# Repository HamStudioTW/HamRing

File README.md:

```                                                                     
  ╭──╮                        ╭──────────────────╮                  
  |  |                        |  ╭────────────╮  |        ╭──────────╮          
  |  │            ╭──╮        |  |            |  |        |  ╭────╮  ╰───────╮  
  |  ╰────────────╯  |        |  ╰────────────╯  |        |  |    |  ╭────╮  |  
  |  ╭────────────╮  |        |  ╭────────────╮  |        |  |    |  |    |  |  
  |  │            │  |        |  │            │  |        |  |    |  |    |  |  
  |  │            │  |        |  │            │  |        |  |    |  |    |  | 
  ╰──╯            ╰──╯        ╰──╯            ╰──╯        ╰──╯    ╰──╯    ╰──╯  Studio
```
# HamRing

"Keychain_Main" is base on ATTiny84a useing Micronucleus Bootloader  
"ESP_Keychain"  is base on ESP-M1(ESP8285) useing Arduino Bootloader  
"AnyWare8051" is base on STC8G1K08  
"OneKey" is base on CH552G useing Arduino Bootloader

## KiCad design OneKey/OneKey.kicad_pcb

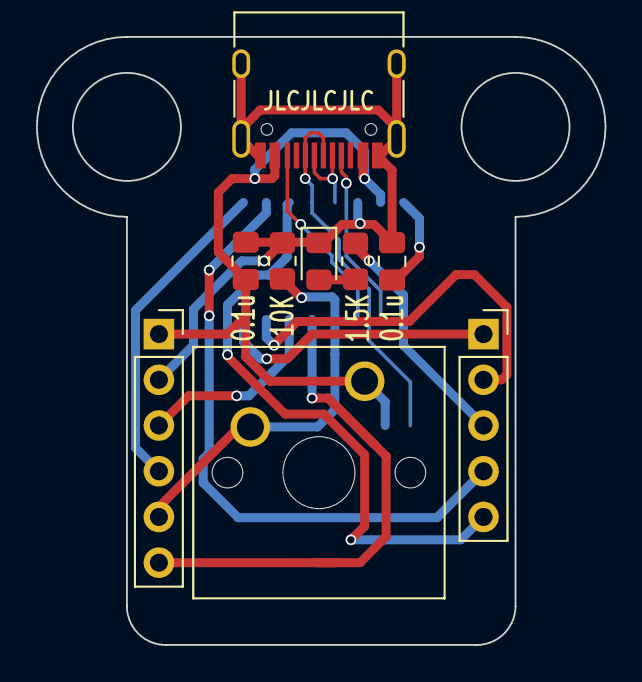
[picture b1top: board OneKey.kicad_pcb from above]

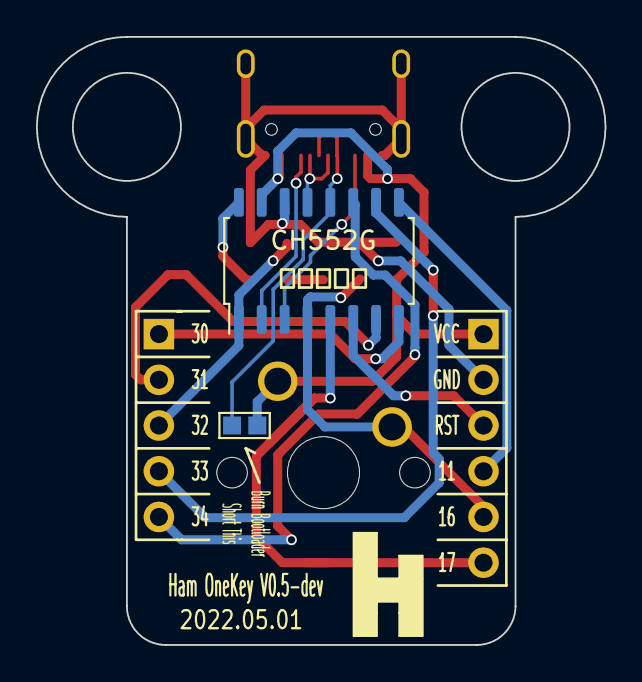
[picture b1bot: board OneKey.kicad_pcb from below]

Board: 2 copper layers, 31.6 x 33.8 mm, 12 parts (3 on the bottom side), 17 nets.

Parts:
0.1u, 0.1u#2: 0.1u; C_0805_2012Metric_Pad1.18x1.45mm_HandSolder
1.5K: 1.5K; R_0805_2012Metric_Pad1.20x1.40mm_HandSolder
10K: 10K; R_0805_2012Metric_Pad1.20x1.40mm_HandSolder
CH552G: CH552G; SOIC-16_4.55x10.3mm_P1.27mm
D1: LED; D_0805_2012Metric_Pad1.15x1.40mm_HandSolder
D+: TestPoint_Pad_1.0x1.0mm
J1: USB_C_Receptacle_USB2.0; USB_C_Receptacle_HRO_TYPE-C-31-M-12
J2: Conn_01x06_Female; PinSocket_1x06_P2.54mm_Vertical
J3: Conn_01x05_Female; PinSocket_1x05_P2.54mm_Vertical
SW1: SW_Push; SW_Cherry_MX_1.00u_PCB
VCC: TestPoint_Pad_1.0x1.0mm

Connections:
D+: CH552G.12 (P3.6/UDP), D+.1, J1.A6 (D+), J1.B6 (D+)
D-: CH552G.13 (P3.7/UDM), J1.A7 (D-), J1.B7 (D-)
GND: 0.1u.1, 0.1u#2.1, 10K.1, CH552G.14 (GND), D1.1 (K), J1.A1 (GND), J1.A12 (GND), J1.B1 (GND), J1.B12 (GND), J1.S1 (SHIELD), J2.2
unnamed: 0.1u.2, CH552G.16 (V33)
unnamed: 1.5K.1, D1.2 (A)
P1.1: CH552G.9 (P1.1), J2.4
P1.6: 10K.2, CH552G.4 (P1.6/MISO/RxD1_), J2.5, SW1.2
P1.7: CH552G.5 (P1.7/SCK/TxD1), J2.6
P3.0: CH552G.8 (P3.0/RxD), J3.1
P3.1: CH552G.7 (P3.1/TxD), J3.2
P3.2: 1.5K.2, CH552G.1 (P3.2/TxD1_), J3.3
P3.3: CH552G.10 (P3.3), J3.4
P3.4: CH552G.11 (P3.4/RxD1_), J3.5
RST: CH552G.6 (RST), J2.3
UCC1: CH552G.2 (P1.4), J1.A5 (CC1)
UCC2: CH552G.3 (P1.5/MOSI), J1.B5 (CC2)
VBUS: 0.1u#2.2, CH552G.15 (VCC), J1.A4 (VBUS), J1.A9 (VBUS), J1.B4 (VBUS), J1.B9 (VBUS), J2.1, SW1.1, VCC.1

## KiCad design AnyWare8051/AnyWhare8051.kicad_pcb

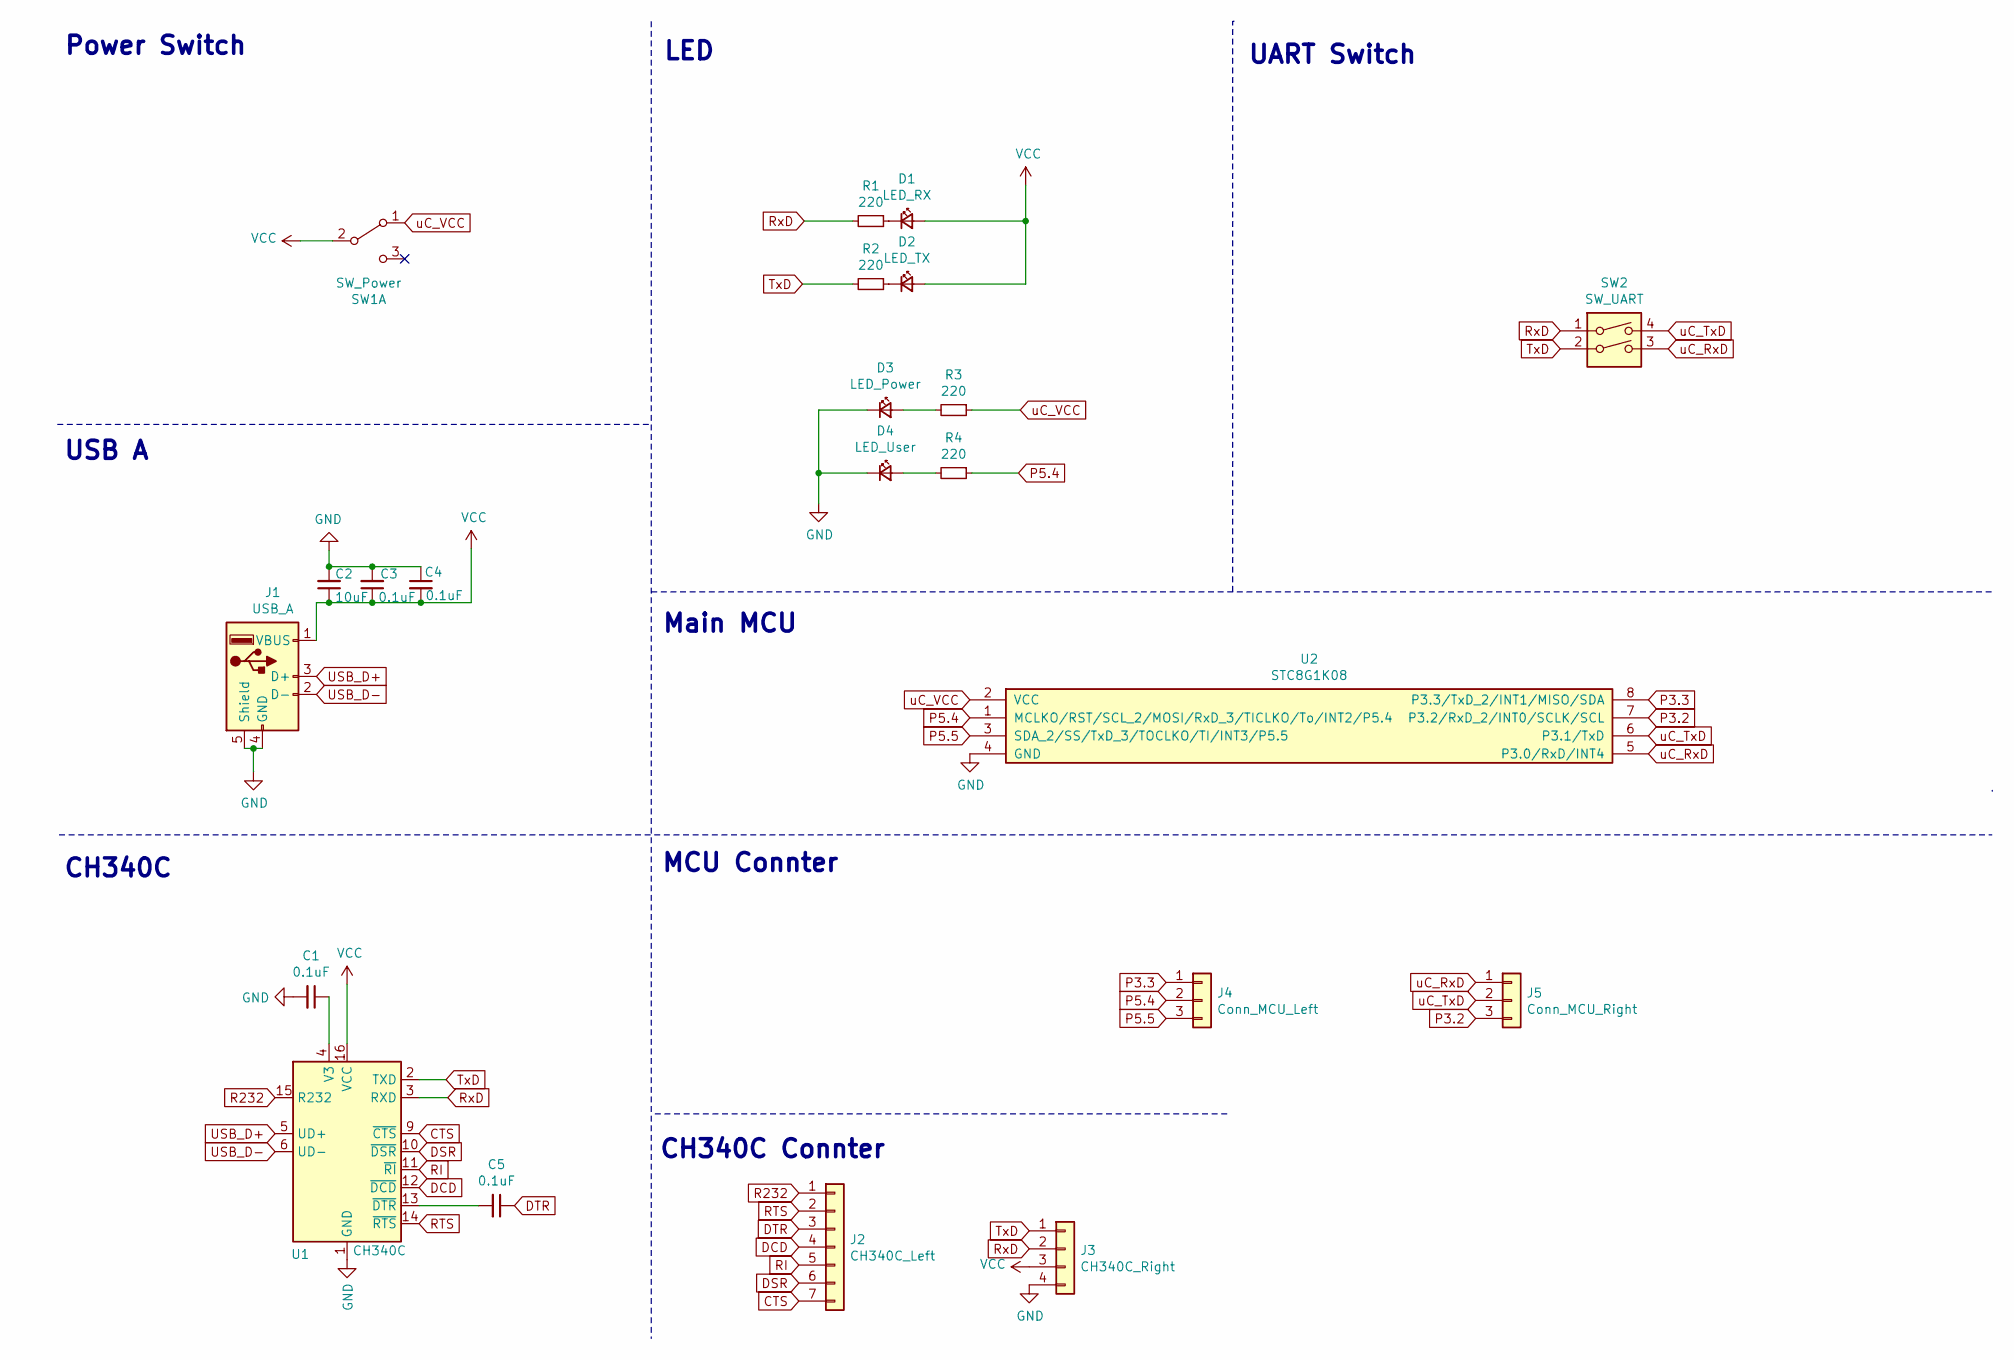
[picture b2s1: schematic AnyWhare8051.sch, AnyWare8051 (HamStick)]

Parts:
C1, C3, C4, C5: 0.1uF; C_0805_2012Metric_Pad1.18x1.45mm_HandSolder
C2: 10uF; C_0805_2012Metric_Pad1.18x1.45mm_HandSolder
D1: LED_RX; LED_0805_2012Metric_Pad1.15x1.40mm_HandSolder
D2: LED_TX; LED_0805_2012Metric_Pad1.15x1.40mm_HandSolder
D3: LED_Power; LED_0805_2012Metric_Pad1.15x1.40mm_HandSolder
D4: LED_User; LED_0805_2012Metric_Pad1.15x1.40mm_HandSolder
J1: USB_A; USB_A_CNCTech_1001-011-01101_Horizontal
J2: CH340C_Left; PinHeader_1x07_P2.54mm_Vertical
J3: CH340C_Right; PinHeader_1x04_P2.54mm_Vertical
J4: Conn_MCU_Left; PinHeader_1x03_P2.54mm_Vertical
J5: Conn_MCU_Right; PinHeader_1x03_P2.54mm_Vertical
R1, R2, R3, R4: 220; R_0805_2012Metric_Pad1.20x1.40mm_HandSolder
SW1: SW_Power; SW_SPDT_PCM12
SW2: SW_UART; SW_DIP_SPSTx02_Slide_6.7x6.64mm_W8.61mm_P2.54mm_LowProfile
U1: CH340C; SOIC-16_3.9x9.9mm_P1.27mm
U2: STC8G1K08; HSOP-8-1EP_3.9x4.9mm_P1.27mm_EP2.41x3.1mm_No_GND

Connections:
CTS: J2.7, U1.9 (~CTS)
DCD: J2.4, U1.12 (~DCD)
DSR: J2.6, U1.10 (~DSR)
DTR: C5.1, J2.3
GND: C1.2, C2.2, C3.2, C4.1, D3.1 (K), D4.1 (K), J1.4 (GND), J1.5 (Shield), J3.4, U1.1 (GND), U2.4 (GND)
unnamed: C1.1, U1.4 (V3)
unnamed: C5.2, U1.13 (~DTR)
unnamed: D1.1 (K), R1.1
unnamed: D2.1 (K), R2.1
unnamed: D3.2 (A), R3.2
unnamed: D4.2 (A), R4.2
P3.2: J5.3, U2.7 (P3.2/RxD_2/INT0/SCLK/SCL)
P3.3: J4.1, U2.8 (P3.3/TxD_2/INT1/MISO/SDA)
P5.4: J4.2, R4.1, U2.1 (MCLKO/RST/SCL_2/MOSI/RxD_3/TICLKO/To/IN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)
P5.5: J4.3, U2.3 (SDA_2/SS/TxD_3/TOCLKO/TI/INT3/P5.5)
R232: J2.1, U1.15 (R232)
RI: J2.5, U1.11 (~RI)
RTS: J2.2, U1.14 (~RTS)
RxD: J3.2, R1.2, SW2.1, U1.3 (RXD)
TxD: J3.1, R2.2, SW2.2, U1.2 (TXD)
USB_D+: J1.3 (D+), U1.5 (UD+)
USB_D-: J1.2 (D-), U1.6 (UD-)
VCC: C2.1, C3.1, C4.2, D1.2 (A), D2.2 (A), J1.1 (VBUS), J3.3, SW1.2 (B), U1.16 (VCC)
uC_RxD: J5.1, SW2.3, U2.5 (P3.0/RxD/INT4)
uC_TxD: J5.2, SW2.4, U2.6 (P3.1/TxD)
uC_VCC: R3.1, SW1.1 (A), U2.2 (VCC)

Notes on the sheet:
CH340C
CH340C Connter
USB A
Power Switch
LED
UART Switch
Main MCU
MCU Connter

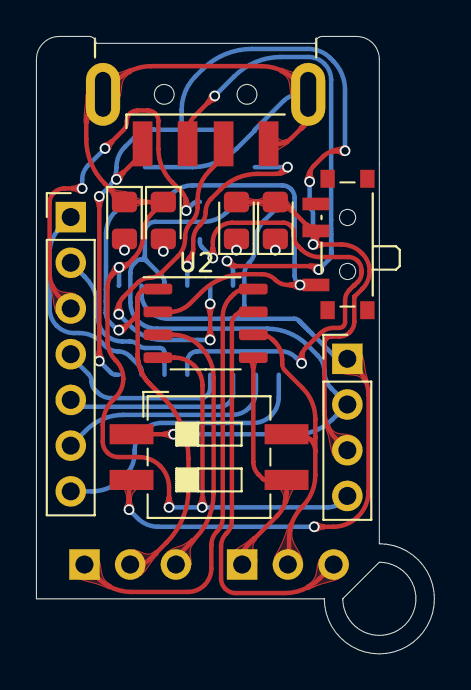
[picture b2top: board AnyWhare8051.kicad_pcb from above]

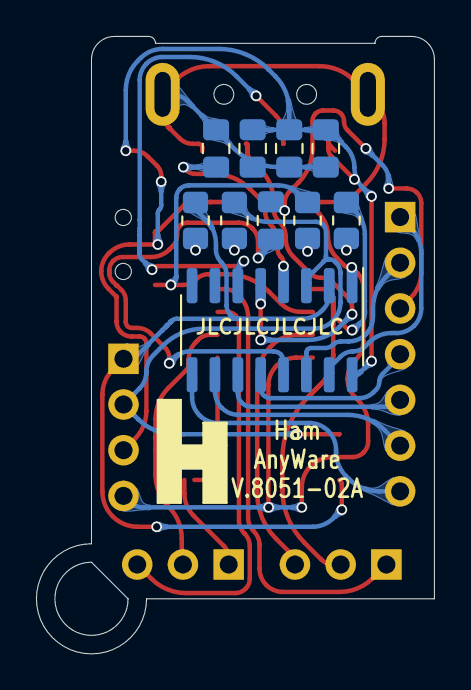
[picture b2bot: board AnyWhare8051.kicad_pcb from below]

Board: 2 copper layers, 22.1 x 34.3 mm, 22 parts (10 on the bottom side), 26 nets.

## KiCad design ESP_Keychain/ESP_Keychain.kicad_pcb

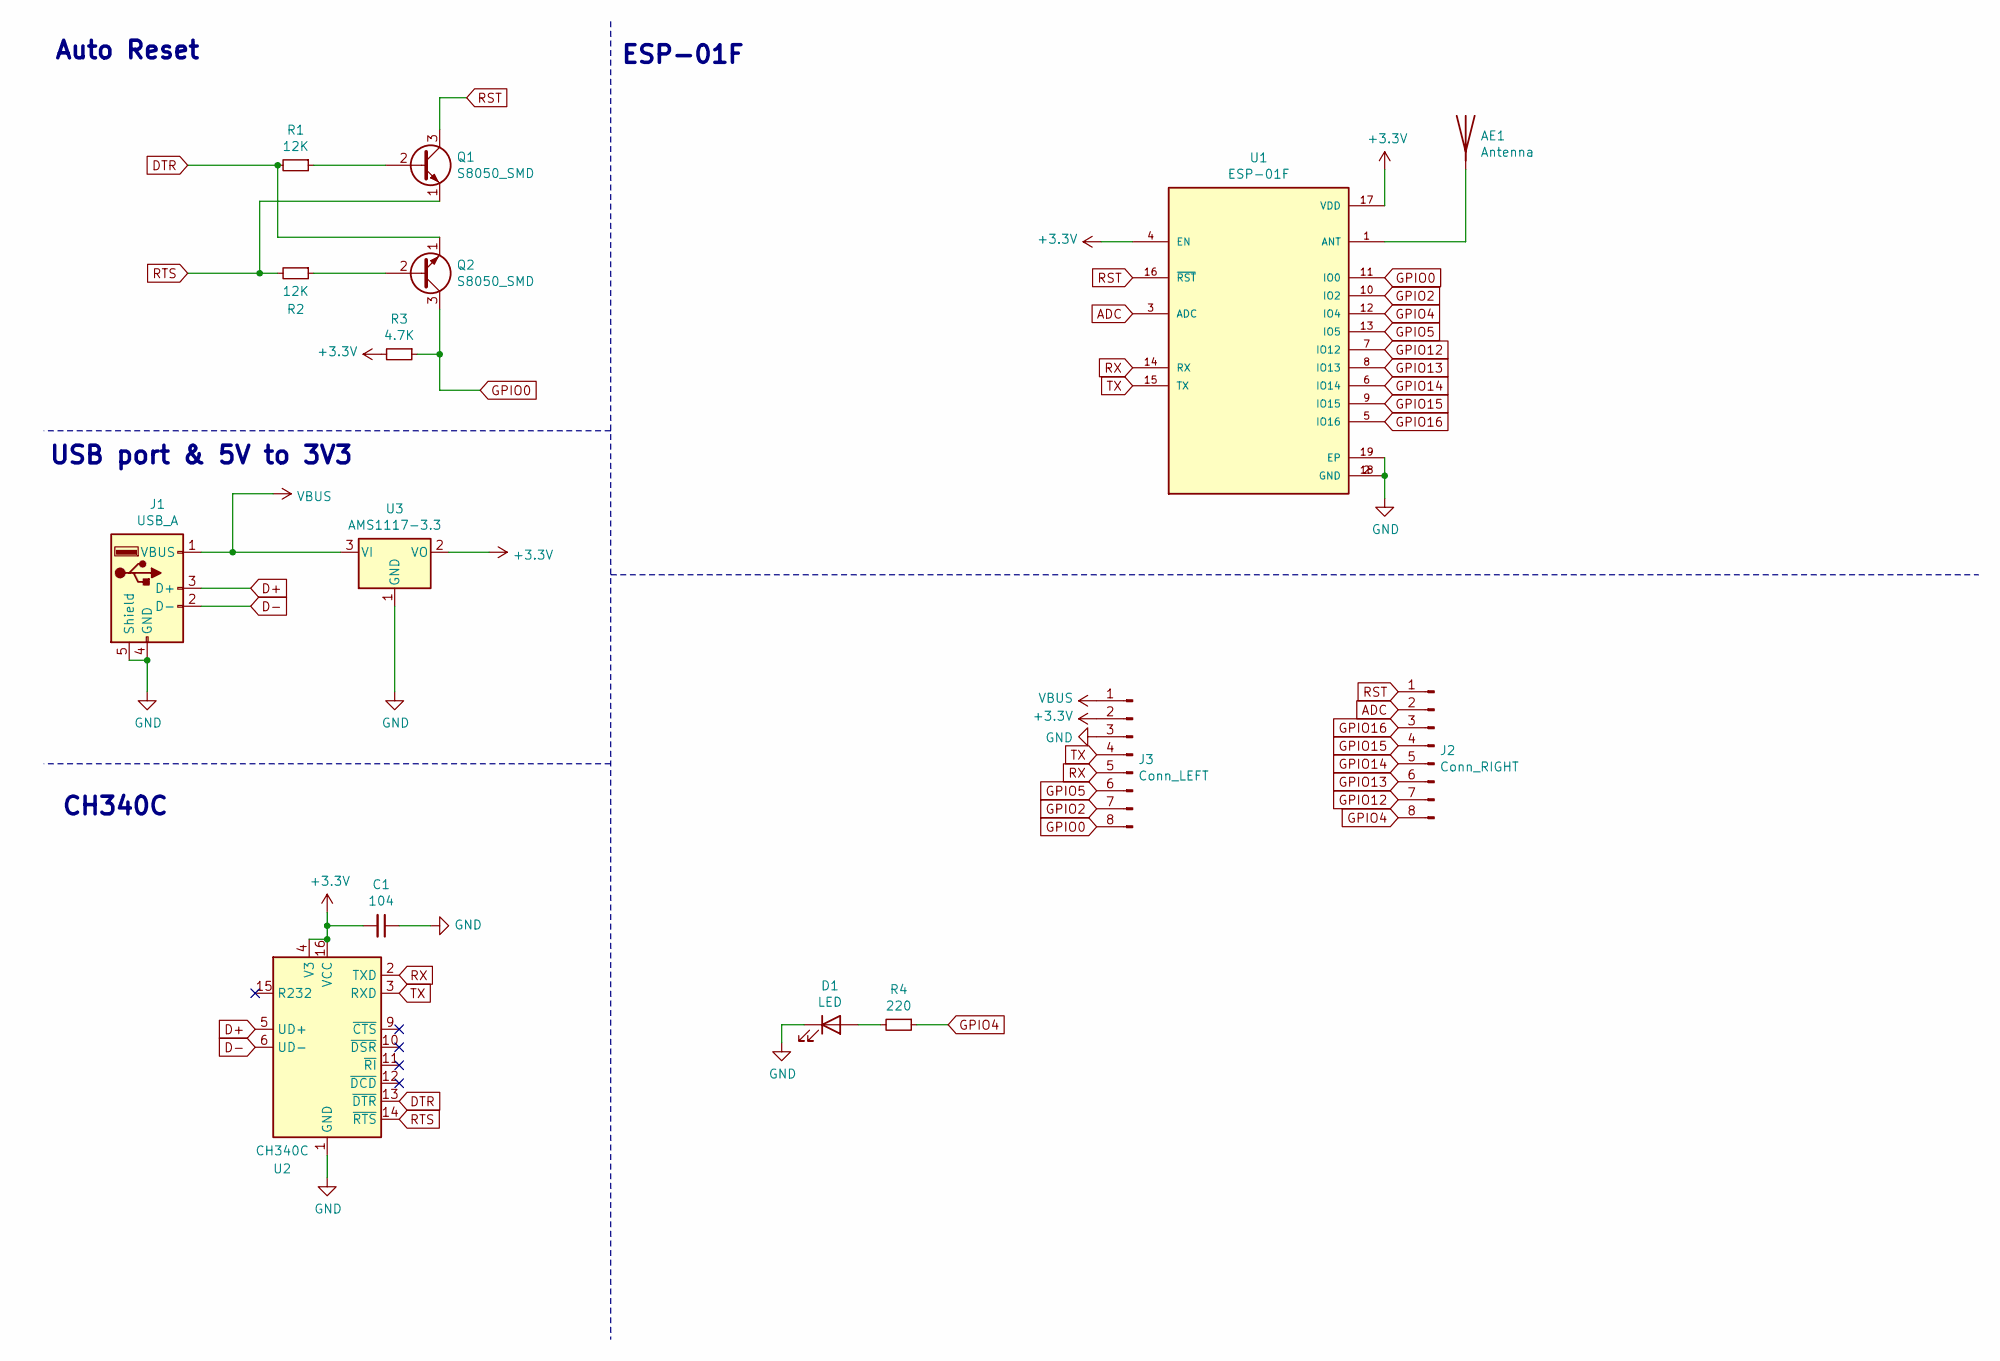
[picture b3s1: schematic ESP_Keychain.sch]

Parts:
AE1: Antenna; Texas_SWRA117D_2.4GHz_Right
C1: 104; C_0805_2012Metric_Pad1.18x1.45mm_HandSolder
D1: LED; LED_0805_2012Metric_Pad1.15x1.40mm_HandSolder
J1: USB_A; USB_A_CNCTech_1001-011-01101_Horizontal
J2: Conn_RIGHT; PinHeader_1x08_P2.54mm_Vertical
J3: Conn_LEFT; PinHeader_1x08_P2.54mm_Vertical
Q1, Q2: S8050_SMD; SOT-23_Handsoldering
R1, R2: 12K; R_0805_2012Metric_Pad1.20x1.40mm_HandSolder
R3: 4.7K; R_0805_2012Metric_Pad1.20x1.40mm_HandSolder
R4: 220; R_0805_2012Metric_Pad1.20x1.40mm_HandSolder
U1: ESP-01F; MODULE_ESP-01F; PARTREV V1
U2: CH340C; SOIC-16_3.9x9.9mm_P1.27mm
U3: AMS1117-3.3; SOT-223-3_TabPin2

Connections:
+3V3: C1.2, J3.2, R3.2, U1.4 (EN), U1.17 (VDD), U2.4 (V3), U2.16 (VCC), U3.2 (VO)
ADC: J2.2, U1.3 (ADC)
D+: J1.3 (D+), U2.5 (UD+)
D-: J1.2 (D-), U2.6 (UD-)
DTR: Q2.1 (E), R1.2, U2.13 (~DTR)
GND: AE1.2, C1.1, D1.1 (K), J1.4 (GND), J1.5 (Shield), J3.3, U1.2 (GND), U1.18 (GND), U1.19 (EP), U2.1 (GND), U3.1 (GND)
GPIO0: J3.8, Q2.3 (C), R3.1, U1.11 (IO0)
GPIO2: J3.7, U1.10 (IO2)
GPIO4: J2.8, R4.1, U1.12 (IO4)
GPIO5: J3.6, U1.13 (IO5)
GPIO12: J2.7, U1.7 (IO12)
GPIO13: J2.6, U1.8 (IO13)
GPIO14: J2.5, U1.6 (IO14)
GPIO15: J2.4, U1.9 (IO15)
GPIO16: J2.3, U1.5 (IO16)
unnamed: AE1.1, U1.1 (ANT)
unnamed: D1.2 (A), R4.2
unnamed: Q1.2 (B), R1.1
unnamed: Q2.2 (B), R2.1
RST: J2.1, Q1.3 (C), U1.16 (~RST)
RTS: Q1.1 (E), R2.2, U2.14 (~RTS)
RX: J3.5, U1.14 (RX), U2.2 (TXD)
TX: J3.4, U1.15 (TX), U2.3 (RXD)
VBUS: J1.1 (VBUS), J3.1, U3.3 (VI)

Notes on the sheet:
Auto Reset
USB port & 5V to 3V3
CH340C
ESP-01F

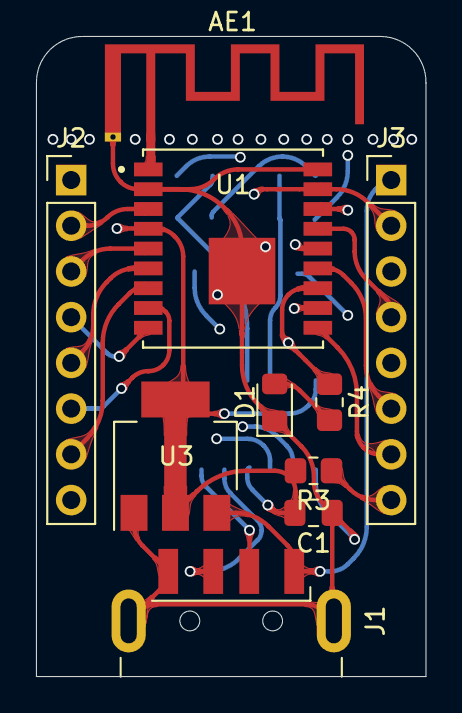
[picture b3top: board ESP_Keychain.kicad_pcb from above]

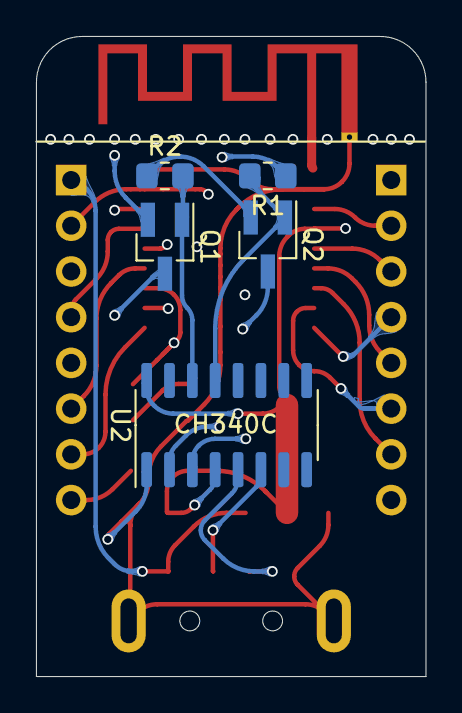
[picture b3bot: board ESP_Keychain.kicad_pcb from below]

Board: 4 copper layers, 21.6 x 35.6 mm, 15 parts (5 on the bottom side), 24 nets.

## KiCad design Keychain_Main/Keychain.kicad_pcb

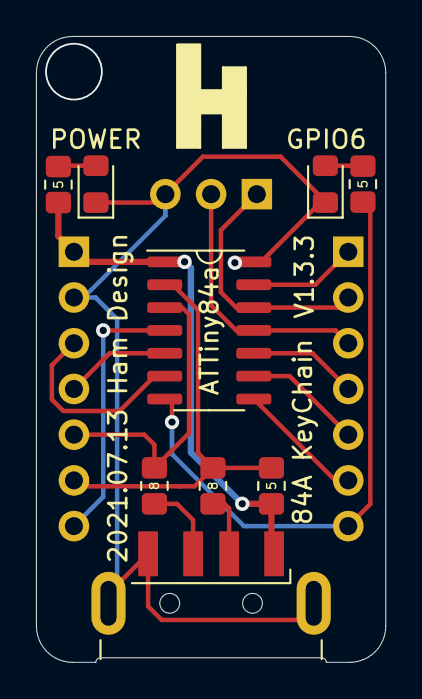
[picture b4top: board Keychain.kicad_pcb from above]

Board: 2 copper layers, 19.4 x 34.8 mm, 13 parts (1 on the bottom side), 18 nets.

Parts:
1.5K, 1.5K#2: 1.5K; R_0805_2012Metric_Pad1.20x1.40mm_HandSolder
C1: 104; R_0805_2012Metric_Pad1.20x1.40mm_HandSolder
D1: POWER; LED_0805_2012Metric_Pad1.15x1.40mm_HandSolder
D2: GPIO6; LED_0805_2012Metric_Pad1.15x1.40mm_HandSolder
J1: USB_A; USB_A_CNCTech_1001-011-01101_Horizontal
J2: Conn_Left; PinSocket_1x07_P2.54mm_Vertical
J3: Conn_Right; PinSocket_1x07_P2.54mm_Vertical
J4: Conn_UART; PinSocket_1x03_P2.54mm_Vertical
R1, R2: 68; R_0805_2012Metric_Pad1.20x1.40mm_HandSolder
R3: 1.5K; R_0805_2012Metric_Pad1.20x1.40mm_HandSolder
U1: ATtiny84A-SSU; SOIC-14_3.9x8.7mm_P1.27mm

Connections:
GND: C1.2, D1.1, D2.1, J1.4, J1.5, J2.2, J4.3, U1.14
unnamed: 1.5K.1, D1.2
unnamed: 1.5K#2.1, D2.2
unnamed: J1.2, R2.1
unnamed: J1.3, R1.1
PA0,0,A0: J3.1, U1.13
PA1,1,A1,TxD: J3.2, J4.1, U1.12
PA2,2,A2,RxD: J3.3, J4.2, U1.11
PA3,3,A3: J3.4, U1.10
PA4,4,A4: J3.5, U1.9
PA5,5,A5: J3.6, U1.8
PA6,6,A6: 1.5K#2.2, J3.7, U1.7
PA7,7,A7: J2.3, U1.6
PB0,10,D-: J2.6, R2.2, R3.2, U1.2
PB1,9,D+: J2.5, R1.2, U1.3
PB2,8: J2.4, U1.5
PB3,11: J2.7, U1.4
VCC: 1.5K.2, C1.1, J1.1, J2.1, R3.1, U1.1

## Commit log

2022-04-20 ATT84a HamRing
2022-04-20 ESP8285 HamRing
2022-05-02 Add OneKey PCB file
    This is base on CH552G HamRing 2in1 dev board
